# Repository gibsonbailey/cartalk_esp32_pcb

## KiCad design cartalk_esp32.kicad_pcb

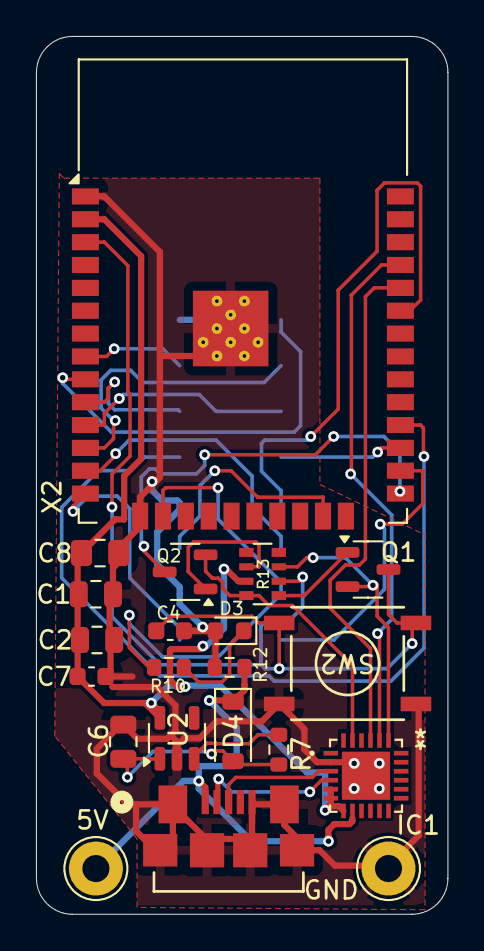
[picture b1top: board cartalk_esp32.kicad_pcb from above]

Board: 2 copper layers, 22.9 x 48.8 mm, 22 parts (1 on the bottom side), 29 nets.

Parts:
C1, C2: 10uF; C_0805_2012Metric
C4, C7: 1uF; C_0603_1608Metric
C6: 10µF; C_0805_2012Metric
C8: 10µF; C_0805_2012Metric_Pad1.18x1.45mm_HandSolder
D3: RED; LED_0603_1608Metric
D4: MBR120; D_SOD-123
IC1: CP2104; QFN50P400X400X80-25N
J1: 10118192-0002LF; CONN_10118192-0002LF_AMP
Q1, Q2: mmbt2222; SOT-23-3
R7, R12: 100K; R_0603_1608Metric
R10: 1K; R_0603_1608Metric
R13: 10K; R_Array_Convex_4x0603
SW2: KMR2; PTS645SL43SMTR92LFS_CNK-L
TP1, TP2: TestPoint; TestPoint_THTPad_D3.0mm_Drill1.5mm
U1: HUB75 Connector Female; Amphenol 2x8 Connector 89898-308ALF
U2: AP2112-3.3; SOT-23-5
X2: ESP32_WROOM32_SKINNY; ESP32-WROOM-32

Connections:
3.3V: C1.1, C2.1, C7.1, C8.1, IC1.5 (VIO), IC1.6 (VDD), IC1.7 (REGIN), R13.3 (1), U2.5 (OUT), X2.2 (3.3V)
/ADDR_A: U1.13 (A), X2.27 (IO16)
/ADDR_B: U1.5 (B), X2.28 (IO17)
/ADDR_C: U1.14 (C), X2.11 (IO26/DAC2/A2_9)
/ADDR_D: U1.6 (D), X2.10 (IO25/DAC1/A2_8)
/B1: R10.1, U1.10 (B1), X2.16 (IO13/A2_4)
/B2: U1.12 (B2), X2.33 (IO21)
/D+: IC1.3 (D+), J1.3 (D+)
/DTR: IC1.23 (DTR), Q2.2 (E), R13.4 (1)
/EN: R7.1, U2.3 (EN)
/G1: U1.1 (G1), X2.14 (IO12/A2_5)
/G2: U1.3 (G2), X2.23 (IO15/A2_3)
/GPIO0: Q2.3 (C), X2.25 (IO0/A2_1)
/LED_CLK: U1.15 (CLK), X2.12 (IO27/A2_7)
/LED_~OE: U1.16 (~OE), X2.9 (IO33/A1_5/X32N)
/R1: U1.9 (R1), X2.26 (IO4/A2_0)
/R2: U1.11 (R2), X2.13 (IO14/A2_6)
/RESET: C4.1, Q1.3 (C), R13.6 (2), SW2.3 (S), SW2.4 (S1), X2.3 (EN)
/RTS: IC1.19 (RTS), Q1.2 (E), R13.7 (2)
/RXD0: IC1.21 (TXD), X2.34 (RXD0)
/STROBE: U1.7 (SRB), X2.8 (IO32/A1_4/X32P)
/TXD0: IC1.20 (RXD), X2.35 (TXD0)
GND: C1.2, C2.2, C4.2, C6.2, C7.2, C8.2, D3.2 (C), IC1.2 (GND), IC1.25 (TP), J1.5 (GND), J1.S1 (SHIELD), J1.S2 (SHIELD__1), J1.S3 (SHIELD__2), J1.S4 (SHIELD__3), J1.S5 (SHIELD__4), J1.S6 (SHIELD__5), R12.1, SW2.1, SW2.2 (P1), TP2.1, U1.2 (GND), U1.4 (GND), U1.8 (GND), U2.2 (GND), X2.1 (GND), X2.15 (GND), X2.39 (BASE_GND)
unnamed: D3.1 (A), R10.2
unnamed: C6.1, D4.2 (C), R7.2, U2.1 (IN)
unnamed: IC1.4 (D-), J1.2 (D-)
unnamed: Q1.1 (B), R13.5 (2)
unnamed: Q2.1 (B), R13.2 (1)
VBUS: D4.1 (A), IC1.8 (VBUS), J1.1 (VCC), R12.2, TP1.1

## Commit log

2024-03-24 Ignore backups.
2024-03-24 Add schematic of esp32 board with direct HUB75 connector.
2024-03-25 First pass of footprint assignments complete.
2024-03-25 Fix USB footprint to match pin names of symbol.
2024-03-25 Fix remaining symbol-footprint pin mismatches.
2024-03-25 Organize the pcb layout some.
2024-03-27 Update component layout on board to fit in a small amount of space.
2024-03-27 Add power pads for soldering on 5V.
2024-03-30 Route tracks on the top layer.
2024-03-30 Route tracks that autorouter couldn't figure out.
2024-03-30 Clean up remaining track fingers.
2024-03-30 Remove ground plane fingers.
2024-03-30 Handle some DRC errors.
2024-03-30 Handle all DRC clearance errors.
2024-03-31 Fix solder mask for CP2104.
2024-03-31 Organize silkscreen.
2024-03-31 Fillet edge cuts. Fix all overlapping silkscreen.
2024-03-31 Modify minimum text height of document to please DRC.
2024-03-31 Add silkscreen to make HUB75 connector orientation obvious.
2024-03-31 Increase track width on VBUS on B.Cu.
2024-03-31 Increase track width on 3.3V on B.Cu.
2024-03-31 Increase track width of GND on B.Cu.
2024-03-31 Increase track width of VBUS on F.Cu.
2024-03-31 Increase track width of 3.3V on F.Cu.
2024-03-31 Increase track width of GND on F.Cu.
2024-04-23 Swap silkscreen labels of D3 and R12 where they should be.
